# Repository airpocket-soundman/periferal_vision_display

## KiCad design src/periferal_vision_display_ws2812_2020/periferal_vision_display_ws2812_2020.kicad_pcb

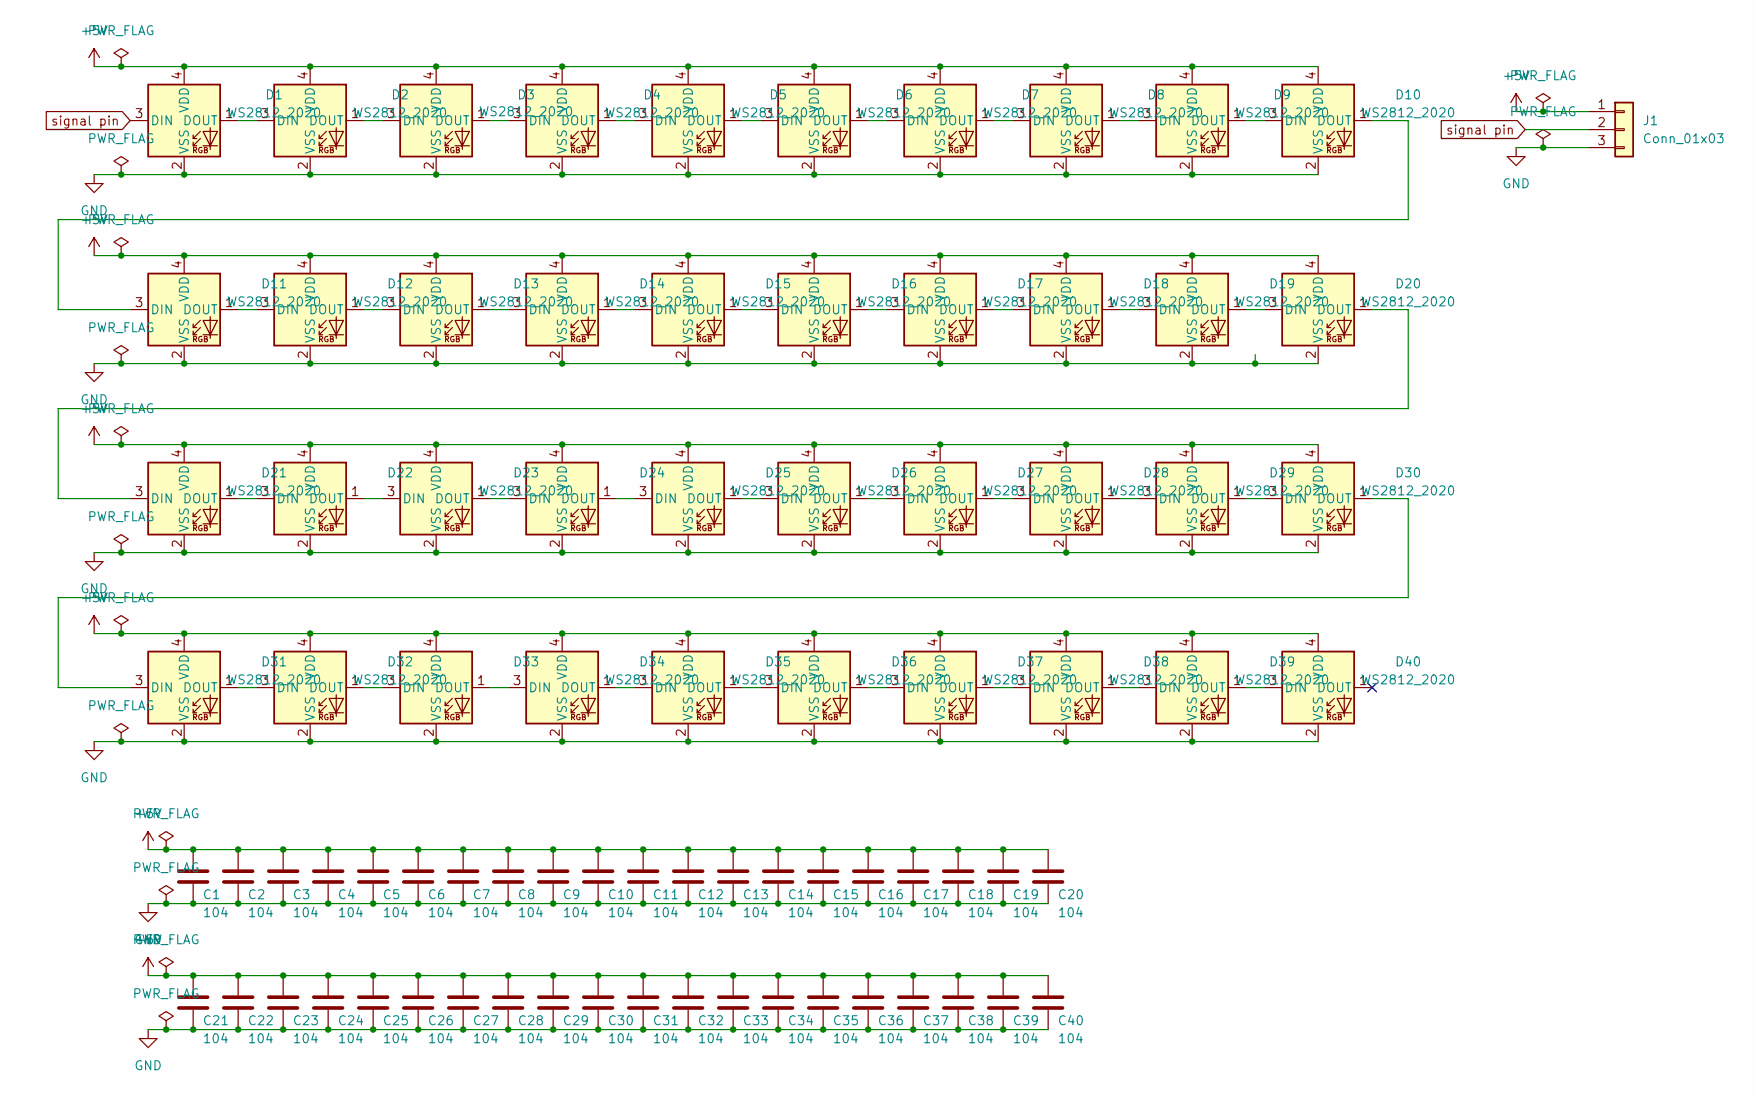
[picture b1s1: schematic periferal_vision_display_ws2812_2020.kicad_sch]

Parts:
C1, C2, C3, C4, C5, C6, C7, C8, C9, C10, C11, C12, C13, C14, C15, C16, C17, C18, C19, C20, C21, C22, C23, C24, C25, C26, C27, C28, C29, C30, C31, C32, C33, C34, C35, C36, C37, C38, C39, C40: 104; C_0201_0603Metric_Pad0.64x0.40mm_HandSolder
D1, D2, D3, D4, D5, D6, D7, D8, D9, D10, D11, D12, D13, D14, D15, D16, D17, D18, D19, D20, D21, D22, D23, D24, D25, D26, D27, D28, D29, D30, D31, D32, D33, D34, D35, D36, D37, D38, D39, D40: WS2812_2020; ws2812_2020
J1: Conn_01x03; pads_3

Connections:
+5V: C1.1, C2.1, C3.1, C4.1, C5.1, C6.1, C7.1, C8.1, C9.1, C10.1, C11.1, C12.1, C13.1, C14.1, C15.1, C16.1, C17.1, C18.1, C19.1, C20.1, C21.1, C22.1, C23.1, C24.1, C25.1, C26.1, C27.1, C28.1, C29.1, C30.1, C31.1, C32.1, C33.1, C34.1, C35.1, C36.1, C37.1, C38.1, C39.1, C40.1, D1.4 (VDD), D2.4 (VDD), D3.4 (VDD), D4.4 (VDD), D5.4 (VDD), D6.4 (VDD), D7.4 (VDD), D8.4 (VDD), D9.4 (VDD), D10.4 (VDD), D11.4 (VDD), D12.4 (VDD), D13.4 (VDD), D14.4 (VDD), D15.4 (VDD), D16.4 (VDD), D17.4 (VDD), D18.4 (VDD), D19.4 (VDD), D20.4 (VDD), D21.4 (VDD), D22.4 (VDD), D23.4 (VDD), D24.4 (VDD), D25.4 (VDD), D26.4 (VDD), D27.4 (VDD), D28.4 (VDD), D29.4 (VDD), D30.4 (VDD), D31.4 (VDD), D32.4 (VDD), D33.4 (VDD), D34.4 (VDD), D35.4 (VDD), D36.4 (VDD), D37.4 (VDD), D38.4 (VDD), D39.4 (VDD), D40.4 (VDD), J1.1
GND: C1.2, C2.2, C3.2, C4.2, C5.2, C6.2, C7.2, C8.2, C9.2, C10.2, C11.2, C12.2, C13.2, C14.2, C15.2, C16.2, C17.2, C18.2, C19.2, C20.2, C21.2, C22.2, C23.2, C24.2, C25.2, C26.2, C27.2, C28.2, C29.2, C30.2, C31.2, C32.2, C33.2, C34.2, C35.2, C36.2, C37.2, C38.2, C39.2, C40.2, D1.2 (VSS), D2.2 (VSS), D3.2 (VSS), D4.2 (VSS), D5.2 (VSS), D6.2 (VSS), D7.2 (VSS), D8.2 (VSS), D9.2 (VSS), D10.2 (VSS), D11.2 (VSS), D12.2 (VSS), D13.2 (VSS), D14.2 (VSS), D15.2 (VSS), D16.2 (VSS), D17.2 (VSS), D18.2 (VSS), D19.2 (VSS), D20.2 (VSS), D21.2 (VSS), D22.2 (VSS), D23.2 (VSS), D24.2 (VSS), D25.2 (VSS), D26.2 (VSS), D27.2 (VSS), D28.2 (VSS), D29.2 (VSS), D30.2 (VSS), D31.2 (VSS), D32.2 (VSS), D33.2 (VSS), D34.2 (VSS), D35.2 (VSS), D36.2 (VSS), D37.2 (VSS), D38.2 (VSS), D39.2 (VSS), D40.2 (VSS), J1.3
unnamed: D1.1 (DOUT), D2.3 (DIN)
unnamed: D2.1 (DOUT), D3.3 (DIN)
unnamed: D3.1 (DOUT), D4.3 (DIN)
unnamed: D4.1 (DOUT), D5.3 (DIN)
unnamed: D5.1 (DOUT), D6.3 (DIN)
unnamed: D6.1 (DOUT), D7.3 (DIN)
unnamed: D7.1 (DOUT), D8.3 (DIN)
unnamed: D8.1 (DOUT), D9.3 (DIN)
unnamed: D9.1 (DOUT), D10.3 (DIN)
unnamed: D10.1 (DOUT), D11.3 (DIN)
unnamed: D11.1 (DOUT), D12.3 (DIN)
unnamed: D12.1 (DOUT), D13.3 (DIN)
unnamed: D13.1 (DOUT), D14.3 (DIN)
unnamed: D14.1 (DOUT), D15.3 (DIN)
unnamed: D15.1 (DOUT), D16.3 (DIN)
unnamed: D16.1 (DOUT), D17.3 (DIN)
unnamed: D17.1 (DOUT), D18.3 (DIN)
unnamed: D18.1 (DOUT), D19.3 (DIN)
unnamed: D19.1 (DOUT), D20.3 (DIN)
unnamed: D20.1 (DOUT), D21.3 (DIN)
unnamed: D21.1 (DOUT), D22.3 (DIN)
unnamed: D22.1 (DOUT), D23.3 (DIN)
unnamed: D23.1 (DOUT), D24.3 (DIN)
unnamed: D24.1 (DOUT), D25.3 (DIN)
unnamed: D25.1 (DOUT), D26.3 (DIN)
unnamed: D26.1 (DOUT), D27.3 (DIN)
unnamed: D27.1 (DOUT), D28.3 (DIN)
unnamed: D28.1 (DOUT), D29.3 (DIN)
unnamed: D29.1 (DOUT), D30.3 (DIN)
unnamed: D30.1 (DOUT), D31.3 (DIN)
unnamed: D31.1 (DOUT), D32.3 (DIN)
unnamed: D32.1 (DOUT), D33.3 (DIN)
unnamed: D33.1 (DOUT), D34.3 (DIN)
unnamed: D34.1 (DOUT), D35.3 (DIN)
unnamed: D35.1 (DOUT), D36.3 (DIN)
unnamed: D36.1 (DOUT), D37.3 (DIN)
unnamed: D37.1 (DOUT), D38.3 (DIN)
unnamed: D38.1 (DOUT), D39.3 (DIN)
unnamed: D39.1 (DOUT), D40.3 (DIN)
signal pin: D1.3 (DIN), J1.2

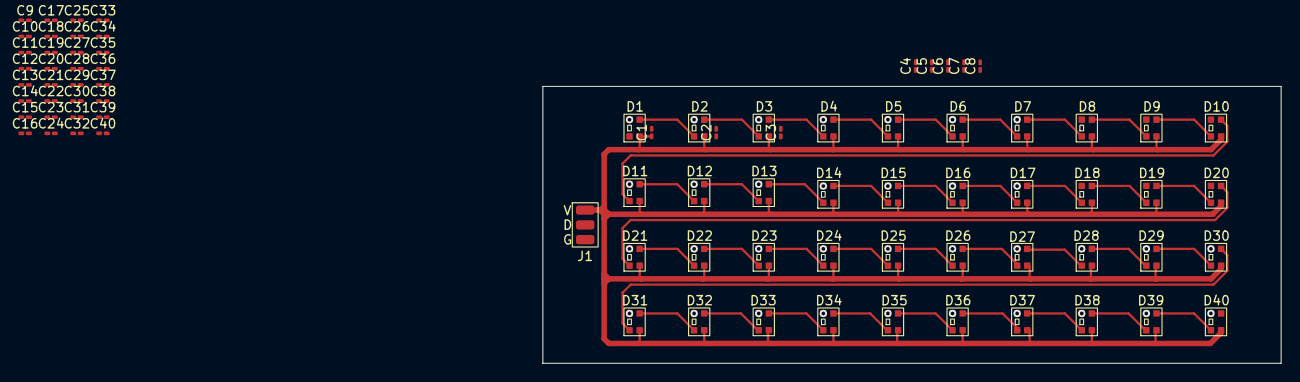
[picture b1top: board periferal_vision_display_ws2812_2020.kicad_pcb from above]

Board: 2 copper layers, 80.0 x 30.0 mm, 81 parts (0 on the bottom side), 42 nets.

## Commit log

2024-12-20 ファイル追加
2024-12-20 demotest
